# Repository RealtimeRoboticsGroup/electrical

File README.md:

# Realtime Robotic Group Electrical Repo

## License

This project is open-source hardware and is licensed under the **Solderpad Hardware License v2.1** (the "License"), which is a permissive license based on the **Apache License, Version 2.0**.

You may use this work under the terms of the Solderpad Hardware License v2.1, or, at your option, under the terms of the Apache License, Version 2.0.

- **Solderpad v2.1:** [Solderpad Hardware License v2.1 - Solderpad Hardware License](https://solderpad.org/licenses/SHL-2.1/)

- **Apache 2.0:** https://www.apache.org/licenses/LICENSE-2.0

**SPDX-License-Identifier:** `Apache-2.0 WITH SHL-2.1`

## License notes for included projects

### 1. For Schematics (Text Block)

Place this near your **Title Block** or in the **Notes** section of your first sheet.

> **LEGAL NOTICE** Copyright © 2026 [Your Name/Organization].
> Licensed under the Solderpad Hardware License v2.1 (the "License");
> you may not use this work except in compliance with the License.
> You may obtain a copy of the License at: [Solderpad Hardware License v2.1 - Solderpad Hardware License](https://solderpad.org/licenses/SHL-2.1/) SPDX-License-Identifier: Apache-2.0 WITH SHL-2.1

### 2. For PCB Silkscreen (Copper/Ink)

Space on a PCB is usually at a premium. You can use this condensed version on the back of the board (Bottom Silkscreen):

> **© 2026 [Your Name]** **Licensed under Solderpad v2.1** **[https://solderpad.org/SHL-2.1/](https://www.google.com/search?q=https://solderpad.org/SHL-2.1/)**

### 3. The OSHWA Logo (The "Gear")

If you want to signal that this is open-source hardware visually, it is common practice to add the **Open Source Hardware Logo** (a gear with a missing tooth) next to the license text. Most CAD libraries (like the SparkFun or Adafruit libraries) already have this logo as a "footprint" you can simply drop onto your board.

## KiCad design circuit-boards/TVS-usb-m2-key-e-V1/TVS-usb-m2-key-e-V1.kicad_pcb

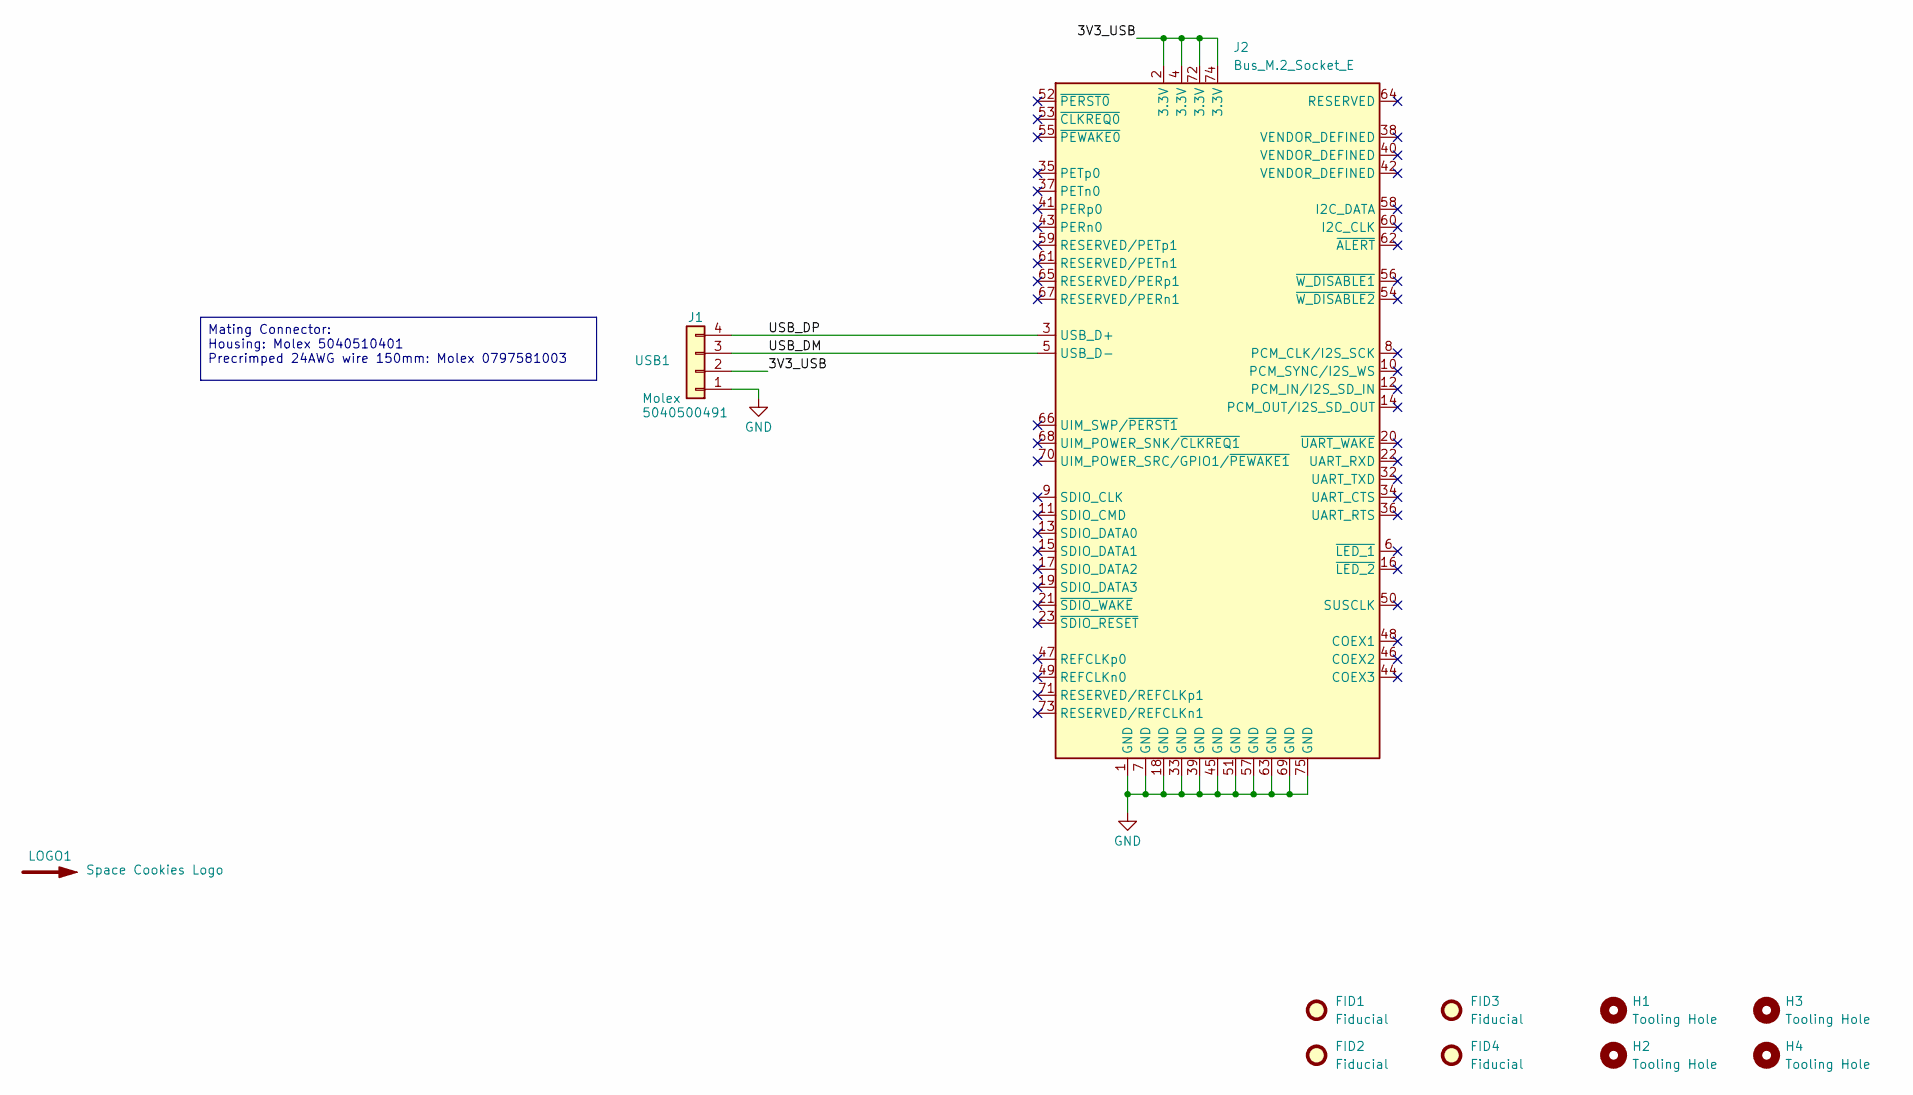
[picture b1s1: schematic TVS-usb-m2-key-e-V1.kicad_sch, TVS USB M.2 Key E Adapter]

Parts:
FID1, FID2, FID3, FID4: Fiducial; Fiducial_1mm_Mask2mm
H1, H2, H3, H4: Tooling Hole; ToolingHole_1.152mm
J1: USB1; Molex-PicoLatch-5040500491; MFG P/N 5040500491; JLCPCB P/N C177235
J2: Bus_M.2_Socket_E; M.2_2230-xx-E
LOGO1: Space Cookies Logo; SPACE_COOKIES_LOGO_7mm

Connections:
/3V3_USB: J1.2, J2.2 (3.3V), J2.4 (3.3V), J2.72 (3.3V), J2.74 (3.3V)
/USB_DM: J1.3, J2.5 (USB_D-)
/USB_DP: J1.4, J2.3 (USB_D+)
GND: J1.1, J2.1 (GND), J2.7 (GND), J2.18 (GND), J2.33 (GND), J2.39 (GND), J2.45 (GND), J2.51 (GND), J2.57 (GND), J2.63 (GND), J2.69 (GND), J2.75 (GND)

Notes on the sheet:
Mating Connector: Housing: Molex 5040510401 Precrimped 24AWG wire 150mm: Molex 0797581003

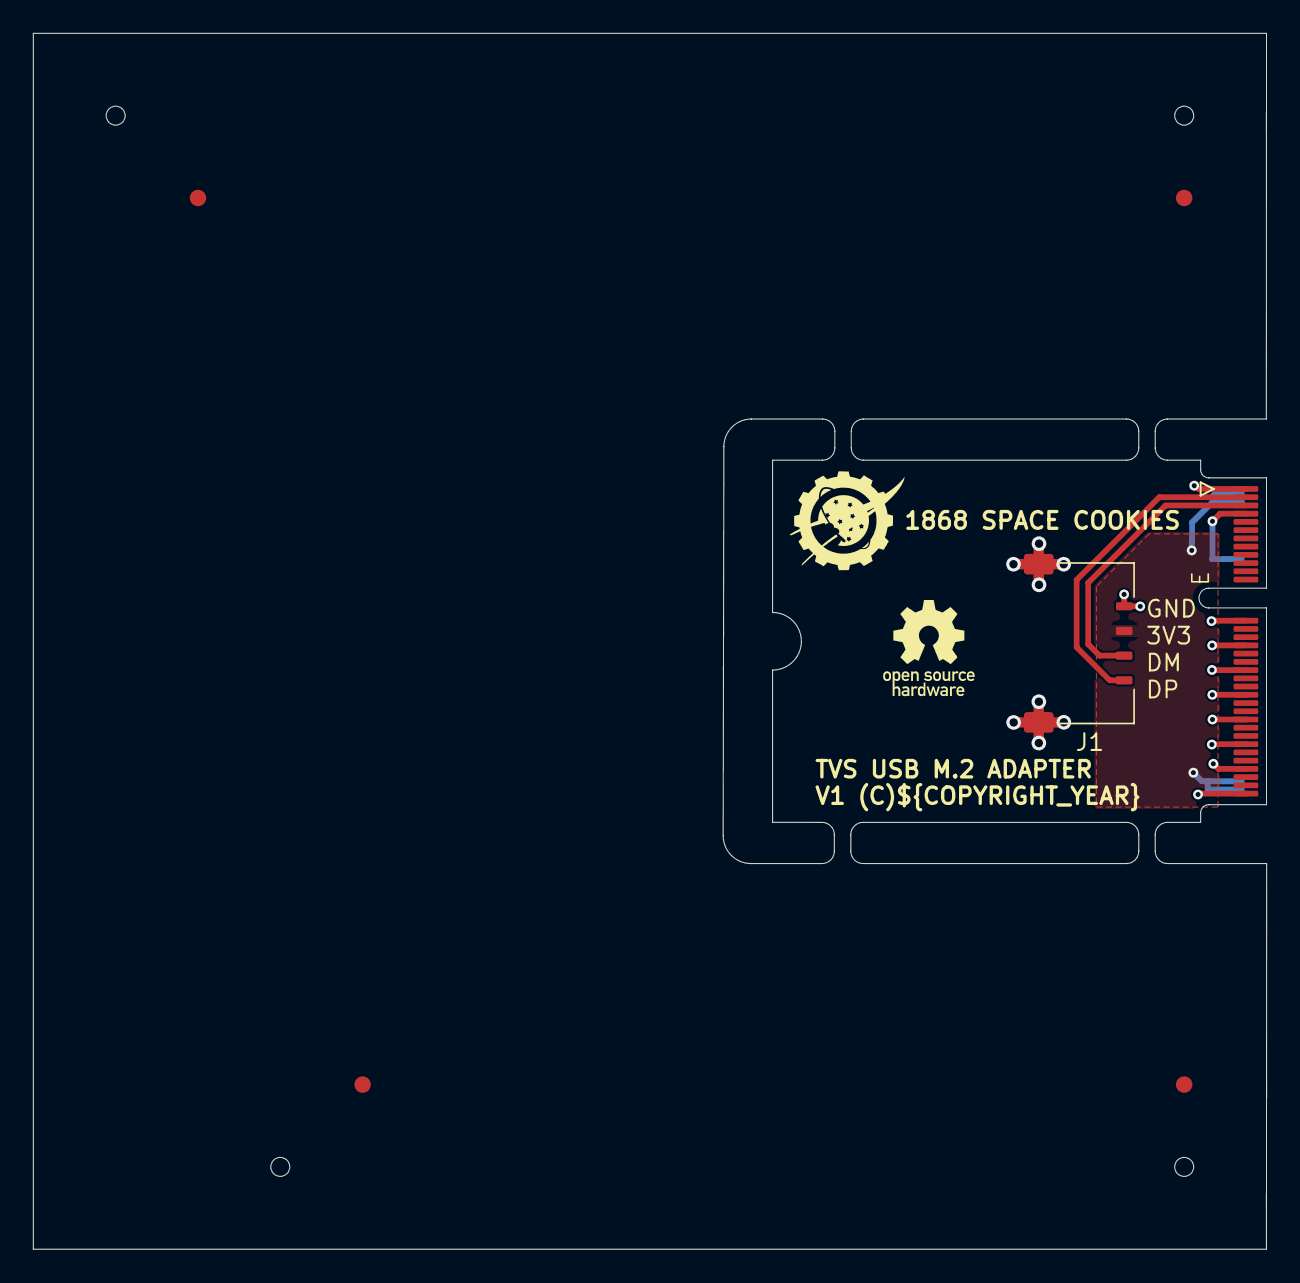
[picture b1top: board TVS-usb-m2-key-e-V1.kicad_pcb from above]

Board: 2 copper layers, 74.9 x 73.8 mm, 11 parts (0 on the bottom side), 4 nets.

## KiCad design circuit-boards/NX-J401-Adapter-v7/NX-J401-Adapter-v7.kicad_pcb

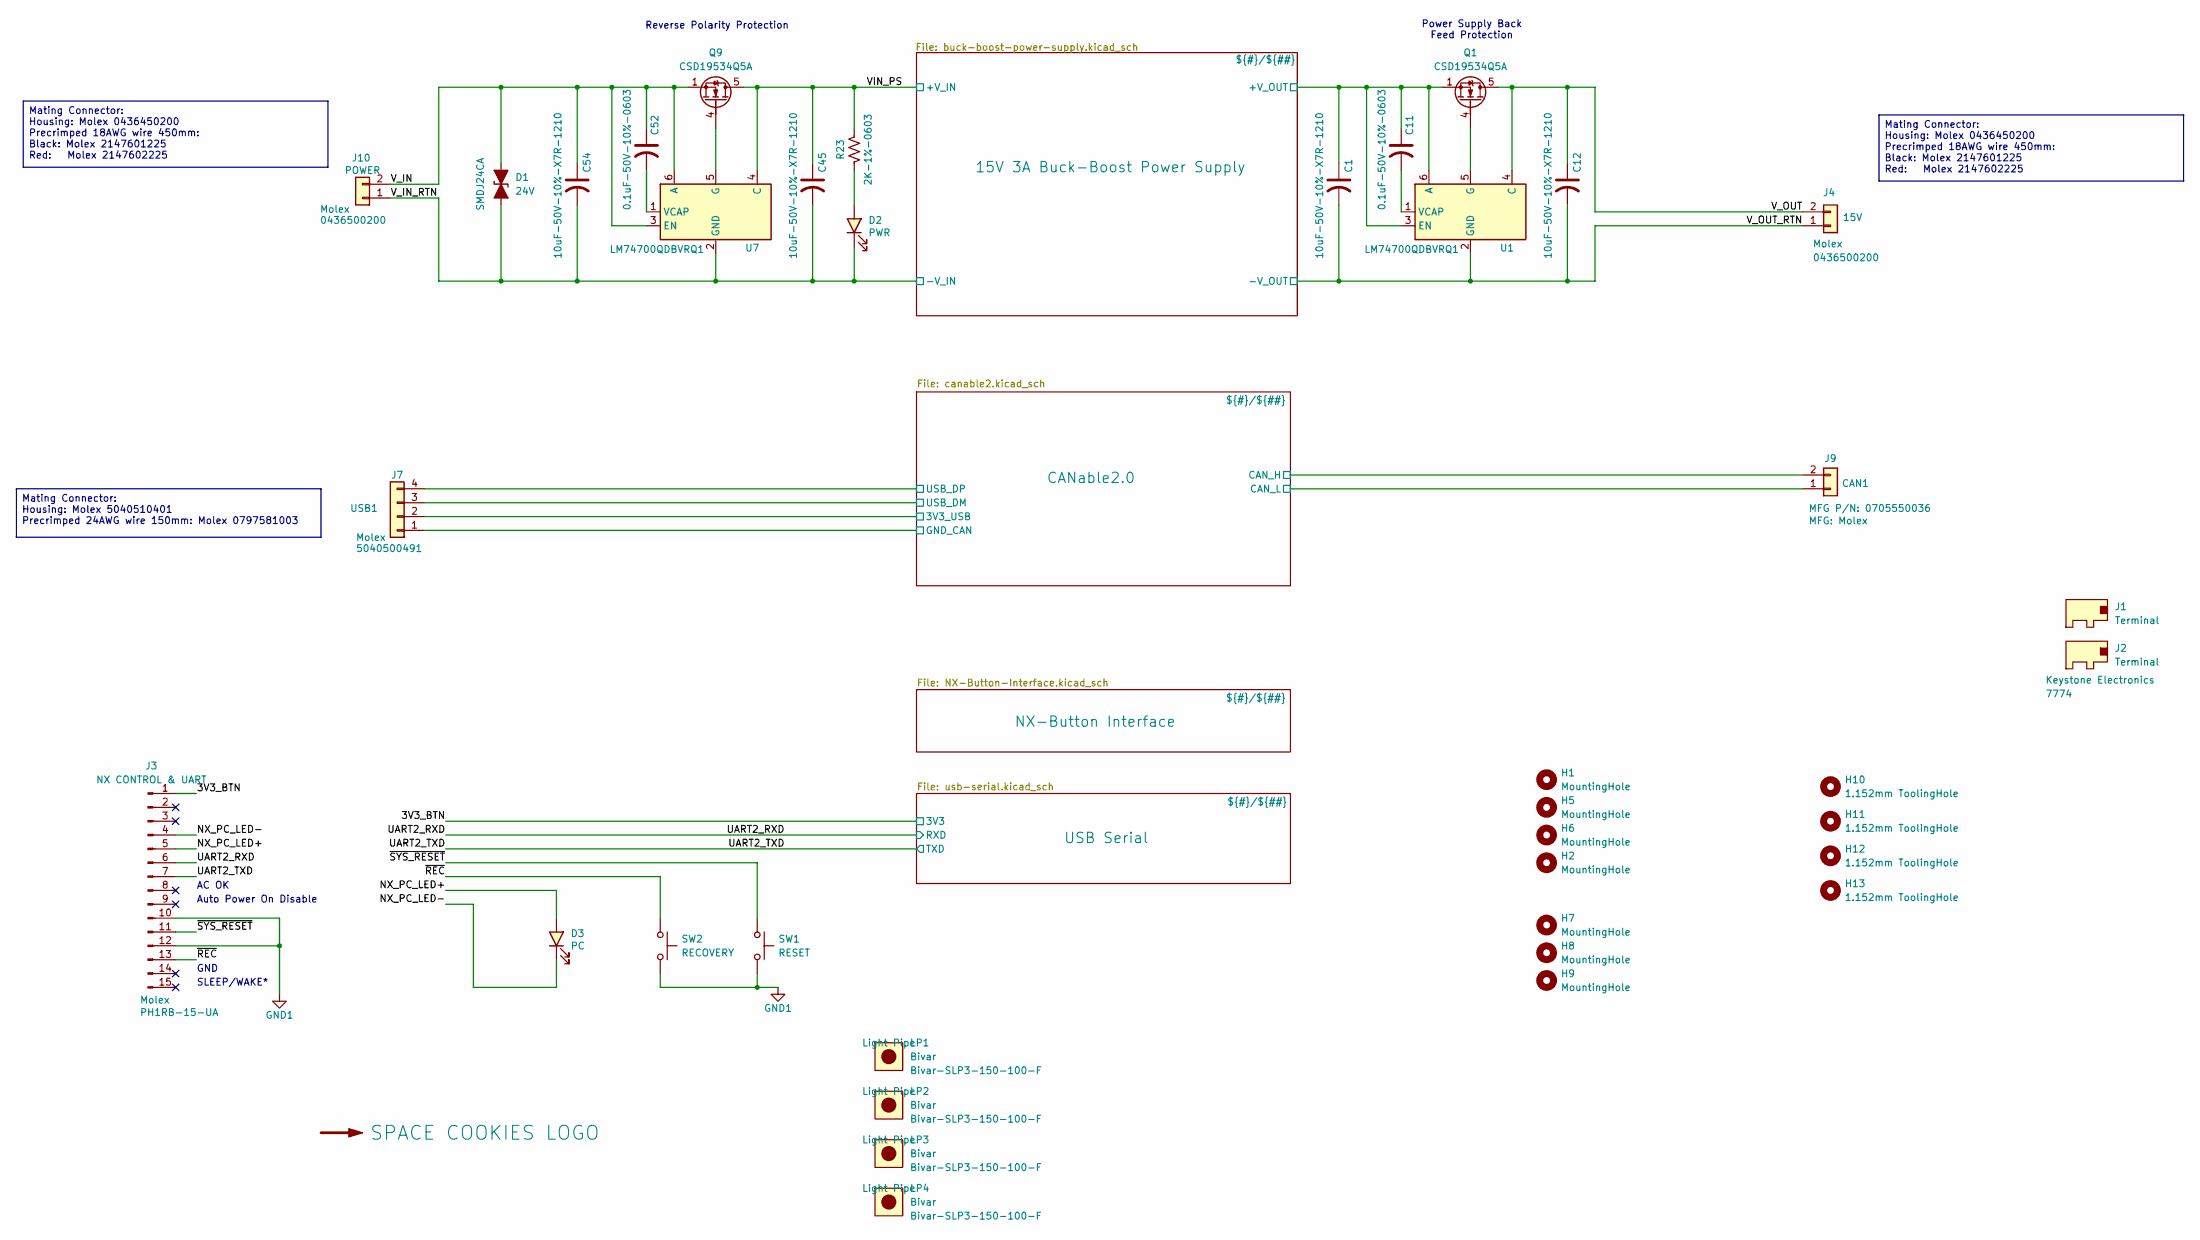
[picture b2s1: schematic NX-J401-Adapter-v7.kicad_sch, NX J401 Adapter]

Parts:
C1, C12, C45, C54: 10uF-50V-10%-X7R-1210; C_1210_3225Metric; MFG P/N GRM32ER71H106KA12L; JLCPCB P/N C77102
C11, C52: 0.1uF-50V-10%-0603; C_0603_1608Metric; MFG P/N CC0603KRX7R9BB104; JLCPCB P/N C14663
D1: 24V; D_SMC_Littelfuse_DO-214AB; MFG P/N SMDJ24CA; JLCPCB P/N C284061
D2: PWR; LED_1206_3216Metric; MFG P/N BL-HGK33-TRB; JLCPCB P/N C5123493
D3: PC; LED_1206_3216Metric; MFG P/N BL-HGK33-TRB; JLCPCB P/N C5123493
H1, H2, H5, H6, H7, H8, H9: MountingHole; MountingHole_2.5mm
H10, H11, H12, H13: 1.152mm ToolingHole; ToolingHole_1.152mm
J1, J2: Terminal; Keystone-7774; MFG P/N 7774; JLCPCB P/N XXXXXX
J3: NX CONTROL & UART; PinHeader_1x15_P2.54mm_Horizontal; MFG P/N PH1RB-15-UA; JLCPCB P/N XXXXXX
J4: 15V; Molex_Micro-Fit_3.0_43650-0200_1x02_P3.00mm_Horizontal; MFG P/N 0436500200; JLCPCB P/N XXXXXX
J7: USB1; Molex-PicoLatch-5040500491; MFG P/N 5040500491; JLCPCB P/N C177235
J9: CAN1; Molex-70555-0001; MFG P/N 0705550036; JLCPCB P/N XXXXXX
J10: POWER; Molex_Micro-Fit_3.0_43650-0200_1x02_P3.00mm_Horizontal; MFG P/N 0436500200; JLCPCB P/N XXXXXX
LOGO1: SPACE COOKIES LOGO; SPACE_COOKIES_LOGO_15mm
LP1, LP2, LP3, LP4: Light Pipe; Bivar-SLP3-150-100-F; MFG P/N Bivar-SLP3-150-100-F; JLCPCB P/N XXXXXX
Q1, Q9: CSD19534Q5A; TI-SON5x6; MFG P/N CSD19534Q5A; JLCPCB P/N C114200
R23: 2K-1%-0603; R_0603_1608Metric; MFG P/N RC0603FR-072KL; JLCPCB P/N C105576
SW1: RESET; SW_TL1105VF100Q_EWI; MFG P/N TL1105VF100Q; JLCPCB P/N XXXXXX
SW2: RECOVERY; SW_TL1105VF100Q_EWI; MFG P/N TL1105VF100Q; JLCPCB P/N XXXXXX
U1, U7: LM74700QDBVRQ1; SOT-23-6; MFG P/N LM74700QDBVRQ1; JLCPCB P/N C2941042

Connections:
/3V3_BTN: J3.1; also elsewhere on the board
/15V 3A Buck-Boost Power Supply/+V_OUT: C1.1, C11.1, Q1.1 (S), Q1.2 (S), Q1.3 (S), U1.3 (EN), U1.6 (A); also elsewhere on the board
/CANable2.0/3V3_USB: J7.2; also elsewhere on the board
/CANable2.0/CAN_H: J9.2; also elsewhere on the board
/CANable2.0/CAN_L: J9.1; also elsewhere on the board
/CANable2.0/GND_CAN: J7.1; also elsewhere on the board
/CANable2.0/USB_DM: J7.3; also elsewhere on the board
/CANable2.0/USB_DP: J7.4; also elsewhere on the board
/NX_PC_LED+: D3.2 (A), J3.5
/NX_PC_LED-: D3.1 (K), J3.4
/UART2_RXD: J3.6; also elsewhere on the board
/UART2_TXD: J3.7; also elsewhere on the board
/VIN_PS: C45.1, Q9.5 (D), R23.1, U7.4 (C); also elsewhere on the board
/V_IN: C52.1, C54.1, D1.2 (A2), J10.2, Q9.1 (S), Q9.2 (S), Q9.3 (S), U7.3 (EN), U7.6 (A)
/V_OUT: C12.1, J4.2, Q1.5 (D), U1.4 (C)
/~REC: J3.13, SW2.1
/~SYS_RESET: J3.11, SW1.1
GND: C1.2, C12.2, C45.2, C54.2, D1.1 (A1), D2.1 (K), J4.1, J10.1, U1.2 (GND), U7.2 (GND); also elsewhere on the board
GND1: J3.10, J3.12, SW1.2, SW2.2; also elsewhere on the board
unnamed: D2.2 (A), R23.2
unnamed: Q1.4 (G), U1.5 (G)
unnamed: Q9.4 (G), U7.5 (G)
unnamed: C11.2, U1.1 (VCAP)
unnamed: C52.2, U7.1 (VCAP)

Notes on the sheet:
GND
Power Supply Back Feed Protection
SLEEP/WAKE*
Reverse Polarity Protection
Auto Power On Disable
AC OK
Mating Connector: Housing: Molex 0436450200 Precrimped 18AWG wire 450mm: Black: Molex 2147601225 Red: Molex 2147602225
Mating Connector: Housing: Molex 5040510401 Precrimped 24AWG wire 150mm: Molex 0797581003

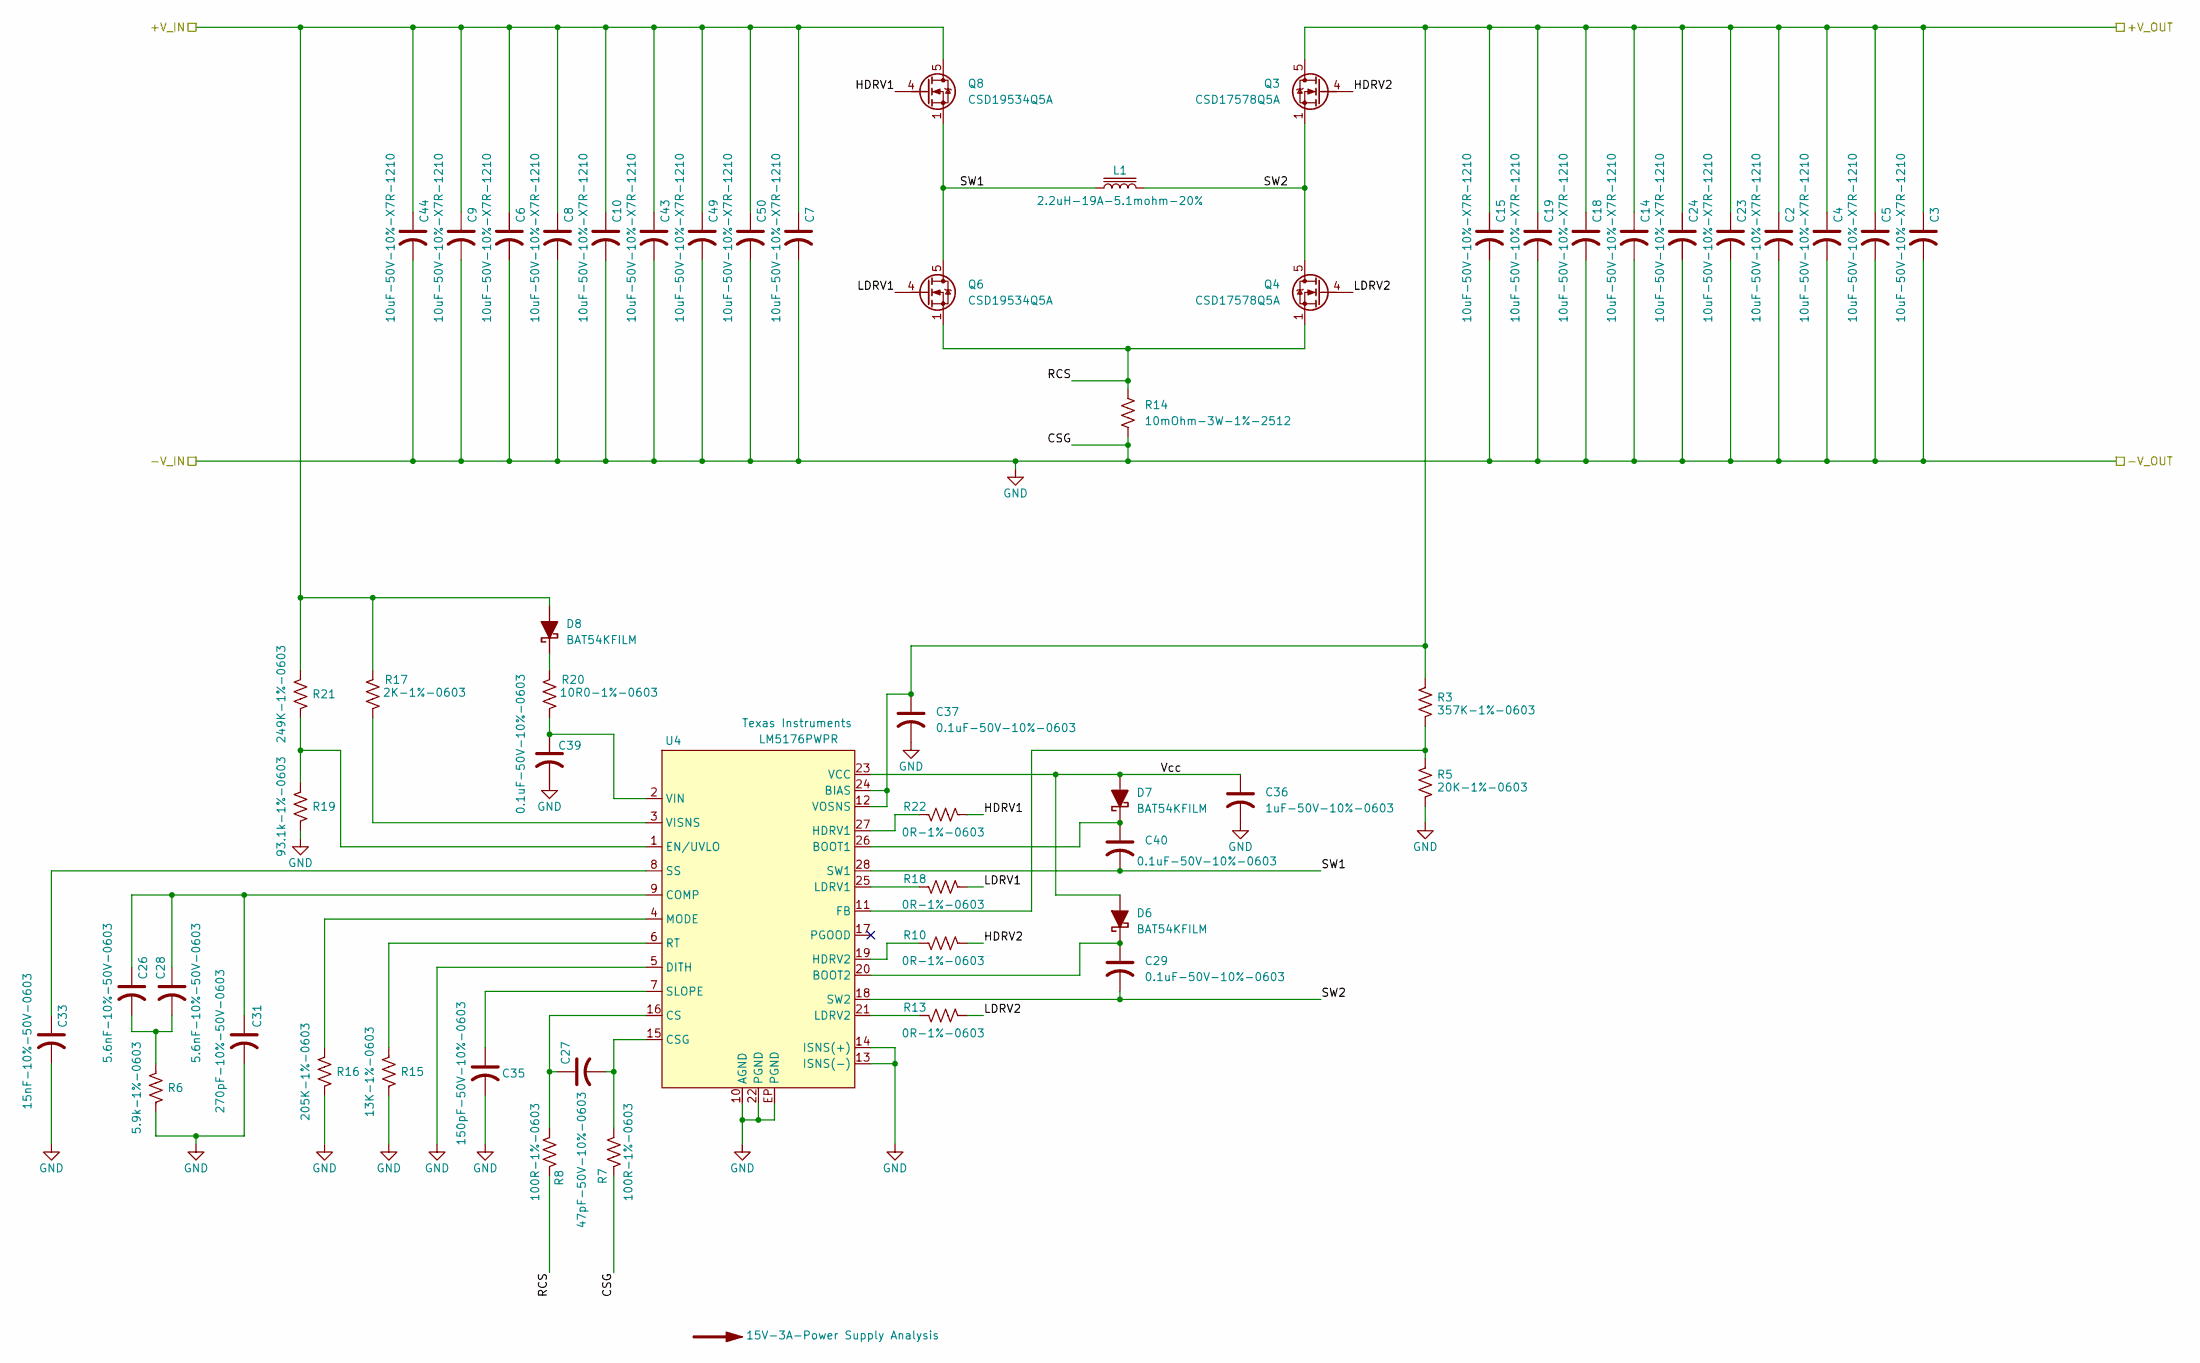
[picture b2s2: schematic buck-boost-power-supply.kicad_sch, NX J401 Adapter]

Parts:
C2, C3, C4, C5, C6, C7, C8, C9, C10, C14, C15, C18, C19, C23, C24, C43, C44, C49, C50: 10uF-50V-10%-X7R-1210; C_1210_3225Metric; MFG P/N GRM32ER71H106KA12L; JLCPCB P/N C77102
C26, C28: 5.6nF-10%-50V-0603; C_0603_1608Metric; MFG P/N CC0603KRX7R9BB562; JLCPCB P/N C107095
C27: 47pF-50V-10%-0603; C_0603_1608Metric; MFG P/N C0603C470K5GACAUTO; JLCPCB P/N C2168903
C29, C37, C39, C40: 0.1uF-50V-10%-0603; C_0603_1608Metric; MFG P/N CC0603KRX7R9BB104; JLCPCB P/N C14663
C31: 270pF-10%-50V-0603; C_0603_1608Metric; MFG P/N CC0603KRX7R9BB271; JLCPCB P/N C107084
C33: 15nF-10%-50V-0603; C_0603_1608Metric; MFG P/N CC0603KRX7R9BB153; JLCPCB P/N C107076
C35: 150pF-50V-10%-0603; C_0603_1608Metric; MFG P/N CC0603KRX7R9BB151; JLCPCB P/N C107075
C36: 1uF-50V-10%-0603; C_0603_1608Metric; MFG P/N UMK107AB7105KA-T; JLCPCB P/N C105174
D6, D7, D8: BAT54KFILM; D_SOD-523; MFG P/N STMicroelectronics; JLCPCB P/N C283259
L1: 2.2uH-19A-5.1mohm-20%; Koher-MDA1050; MFG P/N MDA1050-2R2M; JLCPCB P/N C2847559
Q3, Q4: CSD17578Q5A; TI-SON5x6; MFG P/N CSD17578Q5A; JLCPCB P/N C2871447
Q6, Q8: CSD19534Q5A; TI-SON5x6; MFG P/N CSD19534Q5A; JLCPCB P/N C114200
R3: 357K-1%-0603; R_0603_1608Metric; MFG P/N AC0603FR-07357KL; JLCPCB P/N C227834
R5: 20K-1%-0603; R_0603_1608Metric; MFG P/N RC0603FR-0720KL; JLCPCB P/N C105575
R6: 5.9k-1%-0603; R_0603_1608Metric; MFG P/N 0603WAF5901T5E; JLCPCB P/N C23071
R7, R8: 100R-1%-0603; R_0603_1608Metric; MFG P/N RC0603FR-07100RL; JLCPCB P/N C105588
R10, R13, R18, R22: 0R-1%-0603; R_0603_1608Metric; MFG P/N RC0603FR-070RL; JLCPCB P/N C100044
R14: 10mOhm-3W-1%-2512; R_2512_6332Metric; MFG P/N PA2512FKF7T0R01E; JLCPCB P/N C723413
R15: 13K-1%-0603; R_0603_1608Metric; MFG P/N RC0603FR-0713KL; JLCPCB P/N C137796
R16: 205K-1%-0603; R_0603_1608Metric; MFG P/N 0603WAF2053T5E; JLCPCB P/N C22949
R17: 2K-1%-0603; R_0603_1608Metric; MFG P/N RC0603FR-072KL; JLCPCB P/N C105576
R19: 93.1k-1%-0603; R_0603_1608Metric; MFG P/N AC0603FR-0793K1L; JLCPCB P/N C228101
R20: 10R0-1%-0603; R_0603_1608Metric; MFG P/N RC0603FR-0710RL; JLCPCB P/N C109318
R21: 249K-1%-0603; R_0603_1608Metric; MFG P/N RT0603FRE07249KL; JLCPCB P/N C706146
U4: LM5176PWPR; HTSSOP-28-1EP_4.4x9.7mm_P0.65mm_EP3.4x9.5mm_ThermalVias; MFG P/N LM5176PWPR; JLCPCB P/N C442493

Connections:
/15V 3A Buck-Boost Power Supply/+V_OUT: C2.1, C3.1, C4.1, C5.1, C14.1, C15.1, C18.1, C19.1, C23.1, C24.1, C37.1, Q3.5 (D), R3.1, U4.12 (VOSNS), U4.24 (BIAS); also elsewhere on the board
/15V 3A Buck-Boost Power Supply/HDRV1: Q8.4 (G), R22.2
/15V 3A Buck-Boost Power Supply/HDRV2: Q3.4 (G), R10.2
/15V 3A Buck-Boost Power Supply/LDRV1: Q6.4 (G), R18.2
/15V 3A Buck-Boost Power Supply/LDRV2: Q4.4 (G), R13.2
/15V 3A Buck-Boost Power Supply/RCS: Q4.1 (S), Q4.2 (S), Q4.3 (S), Q6.1 (S), Q6.2 (S), Q6.3 (S), R8.2, R14.1
/15V 3A Buck-Boost Power Supply/SW1: C40.2, L1.1, Q6.5 (D), Q8.1 (S), Q8.2 (S), Q8.3 (S), U4.28 (SW1)
/15V 3A Buck-Boost Power Supply/SW2: C29.2, L1.2, Q3.1 (S), Q3.2 (S), Q3.3 (S), Q4.5 (D), U4.18 (SW2)
/15V 3A Buck-Boost Power Supply/Vcc: C36.1, D6.2 (A), D7.2 (A), U4.23 (VCC)
/VIN_PS: C6.1, C7.1, C8.1, C9.1, C10.1, C43.1, C44.1, C49.1, C50.1, D8.2 (A), Q8.5 (D), R17.1, R21.1; also elsewhere on the board
GND: C2.2, C3.2, C4.2, C5.2, C6.2, C7.2, C8.2, C9.2, C10.2, C14.2, C15.2, C18.2, C19.2, C23.2, C24.2, C31.2, C33.2, C35.2, C36.2, C37.2, C39.2, C43.2, C44.2, C49.2, C50.2, R5.2, R6.2, R7.1, R14.2, R15.2, R16.2, R19.2, U4.5 (DITH), U4.10 (AGND), U4.13 (ISNS(-)), U4.14 (ISNS(+)), U4.22 (PGND), U4.EP (PGND); also elsewhere on the board
unnamed: C26.2, C28.2, R6.1
unnamed: C29.1, D6.1 (K), U4.20 (BOOT2)
unnamed: C40.1, D7.1 (K), U4.26 (BOOT1)
unnamed: D8.1 (K), R20.1
unnamed: C26.1, C28.1, C31.1, U4.9 (COMP)
unnamed: C27.1, R8.1, U4.16 (CS)
unnamed: C27.2, R7.2, U4.15 (CSG)
unnamed: R19.1, R21.2, U4.1 (EN/UVLO)
unnamed: R3.2, R5.1, U4.11 (FB)
unnamed: R22.1, U4.27 (HDRV1)
unnamed: R10.1, U4.19 (HDRV2)
unnamed: R18.1, U4.25 (LDRV1)
unnamed: R13.1, U4.21 (LDRV2)
unnamed: R16.1, U4.4 (MODE)
unnamed: R15.1, U4.6 (RT)
unnamed: C35.1, U4.7 (SLOPE)
unnamed: C33.1, U4.8 (SS)
unnamed: C39.1, R20.2, U4.2 (VIN)
unnamed: R17.2, U4.3 (VISNS)

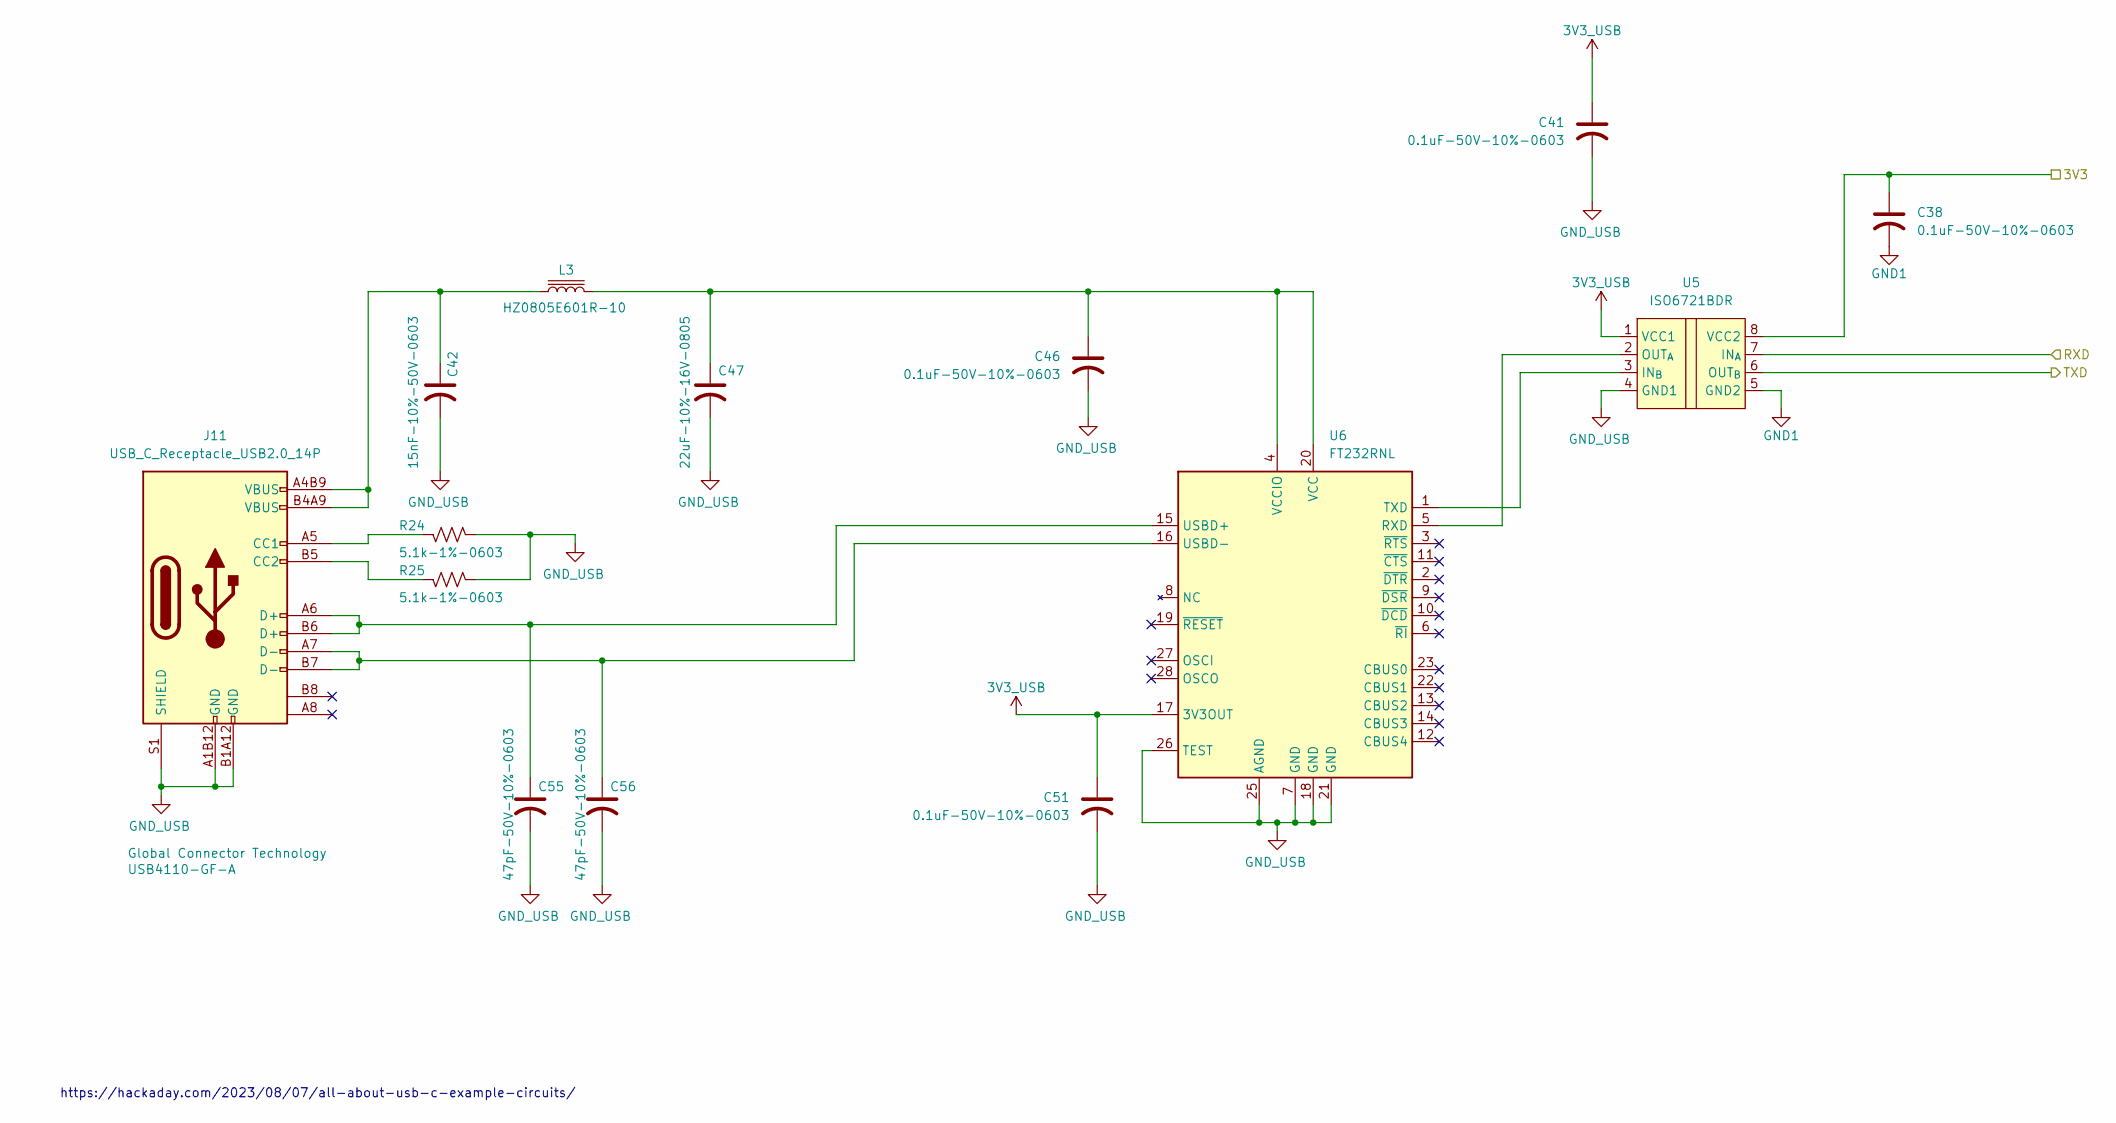
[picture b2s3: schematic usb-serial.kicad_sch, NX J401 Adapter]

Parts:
C38, C41, C46, C51: 0.1uF-50V-10%-0603; C_0603_1608Metric; MFG P/N CC0603KRX7R9BB104; JLCPCB P/N C14663
C42: 15nF-10%-50V-0603; C_0603_1608Metric; MFG P/N CC0603KRX7R9BB153; JLCPCB P/N C107076
C47: 22uF-10%-16V-0805; C_0805_2012Metric; MFG P/N CL21A226KOQNNNE; JLCPCB P/N C296720
C55, C56: 47pF-50V-10%-0603; C_0603_1608Metric; MFG P/N C0603C470K5GACAUTO; JLCPCB P/N C2168903
J11: USB_C_Receptacle_USB2.0_14P; GCT-USB-C-USB4110-GF-A; MFG P/N USB4110-GF-A; JLCPCB P/N C5143397
L3: HZ0805E601R-10; L_0805_2012Metric; MFG P/N HZ0805E601R-10; JLCPCB P/N C2441364
R24, R25: 5.1k-1%-0603; R_0603_1608Metric; MFG P/N RC0603FR-075K1L; JLCPCB P/N C105580
U5: ISO6721BDR; SOIC-8_3.9x4.9mm_P1.27mm; MFG P/N ISO6721BDR; JLCPCB P/N C5216430
U6: FT232RNL; SSOP-28_5.3x10.2mm_P0.65mm; MFG P/N FT232RNL; JLCPCB P/N C8690

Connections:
3V3_USB: C41.1, C51.1, U5.1 (VCC1), U6.17 (3V3OUT)
/3V3_BTN: C38.1, U5.8 (VCC2); also elsewhere on the board
/UART2_RXD: U5.7 (IN_{A}); also elsewhere on the board
/UART2_TXD: U5.6 (OUT_{B}); also elsewhere on the board
GND1: C38.2, U5.5 (GND2); also elsewhere on the board
GND_USB: C41.2, C42.2, C46.2, C47.2, C51.2, C55.2, C56.2, J11.A1B12 (GND), J11.B1A12 (GND), J11.S1 (SHIELD), R24.2, R25.2, U5.4 (GND1), U6.7 (GND), U6.18 (GND), U6.21 (GND), U6.25 (AGND), U6.26 (TEST)
unnamed: C42.1, J11.A4B9 (VBUS), J11.B4A9 (VBUS), L3.1
unnamed: J11.A5 (CC1), R24.1
unnamed: J11.B5 (CC2), R25.1
unnamed: U5.3 (IN_{B}), U6.1 (TXD)
unnamed: U5.2 (OUT_{A}), U6.5 (RXD)
unnamed: C55.1, J11.A6 (D+), J11.B6 (D+), U6.15 (USBD+)
unnamed: C56.1, J11.A7 (D-), J11.B7 (D-), U6.16 (USBD-)
unnamed: C46.1, C47.1, L3.2, U6.4 (VCCIO), U6.20 (VCC)

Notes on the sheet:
https://hackaday.com/2023/08/07/all-about-usb-c-example-circuits/

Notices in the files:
circuit-boards/mag-encoder/mag-encoder.kicad_pcb:
(C)2025 1868
parts and their libraries:
Copyright 2021 Accelerated Designs. All rights reserved.
